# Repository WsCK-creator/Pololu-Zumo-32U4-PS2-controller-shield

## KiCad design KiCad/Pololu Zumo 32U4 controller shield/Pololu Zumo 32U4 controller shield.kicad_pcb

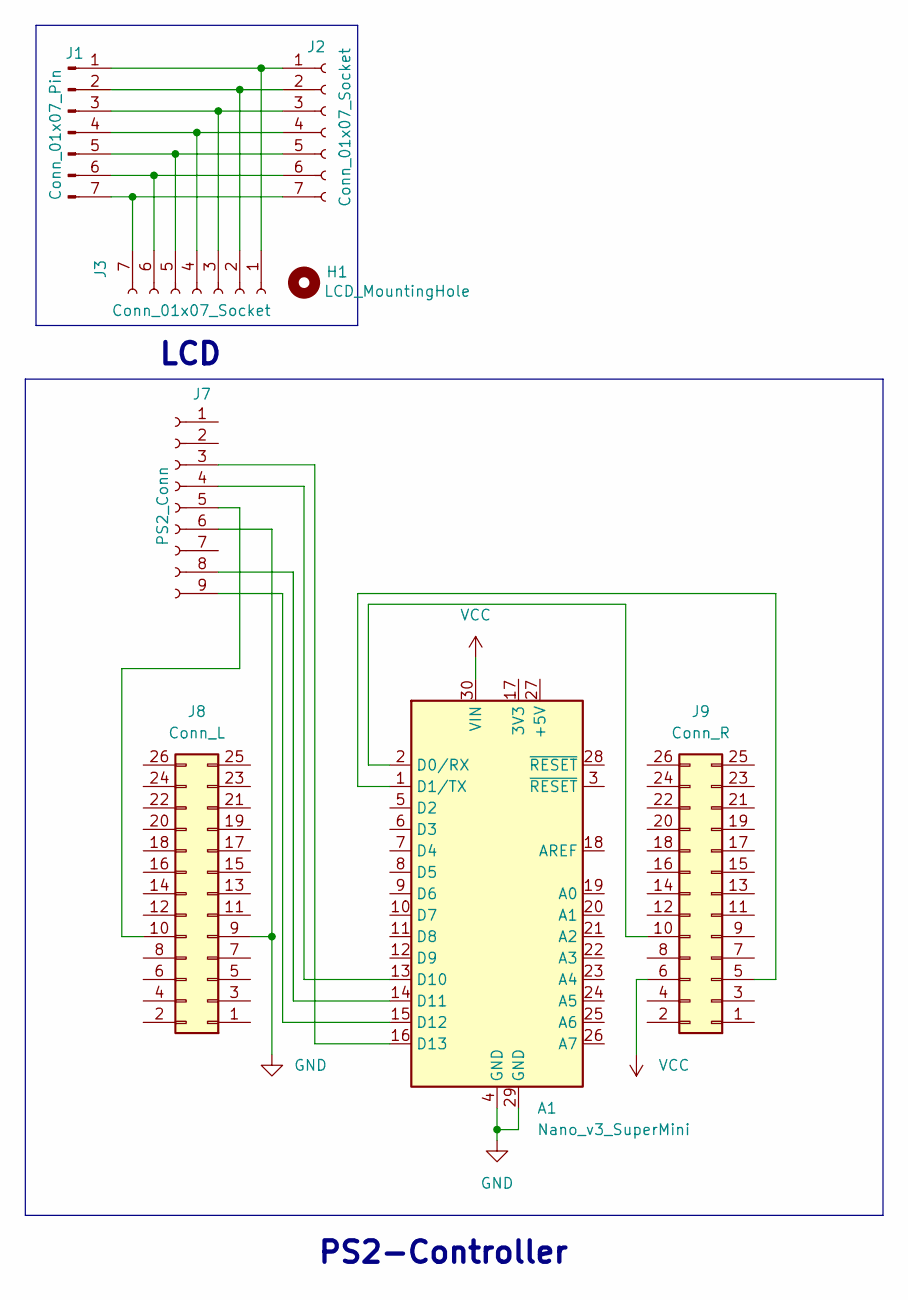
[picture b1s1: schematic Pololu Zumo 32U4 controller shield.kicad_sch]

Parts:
A1: Nano_v3_SuperMini; Nano_V3_SuperMini
H1: LCD_MountingHole; MountingHole_2.2mm_M2
J1: Conn_01x07_Pin; PinHeader_1x07_P2.54mm_Vertical
J2: Conn_01x07_Socket; PinSocket_1x07_P2.54mm_Vertical
J3: Conn_01x07_Socket; PinSocket_1x07_P2.54mm_Vertical_SMD_Pin1Left
J7: PS2_Conn; PS2_Controller_Conn
J8: Conn_L; PinHeader_2x13_P2.54mm_Vertical
J9: Conn_R; PinHeader_2x13_P2.54mm_Vertical

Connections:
GND: A1.4 (GND), A1.29 (GND), J7.6, J8.9
unnamed: A1.2 (D0/RX), J9.10
unnamed: A1.1 (D1/TX), J9.5
unnamed: A1.13 (D10), J7.4
unnamed: A1.14 (D11), J7.8
unnamed: A1.15 (D12), J7.9
unnamed: A1.16 (D13), J7.3
unnamed: J1.1, J2.1, J3.1
unnamed: J1.2, J2.2, J3.2
unnamed: J1.3, J2.3, J3.3
unnamed: J1.4, J2.4, J3.4
unnamed: J1.5, J2.5, J3.5
unnamed: J1.6, J2.6, J3.6
unnamed: J1.7, J2.7, J3.7
unnamed: J7.5, J8.10
VCC: A1.30 (VIN), J9.6

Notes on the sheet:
LCD
PS2-Controller

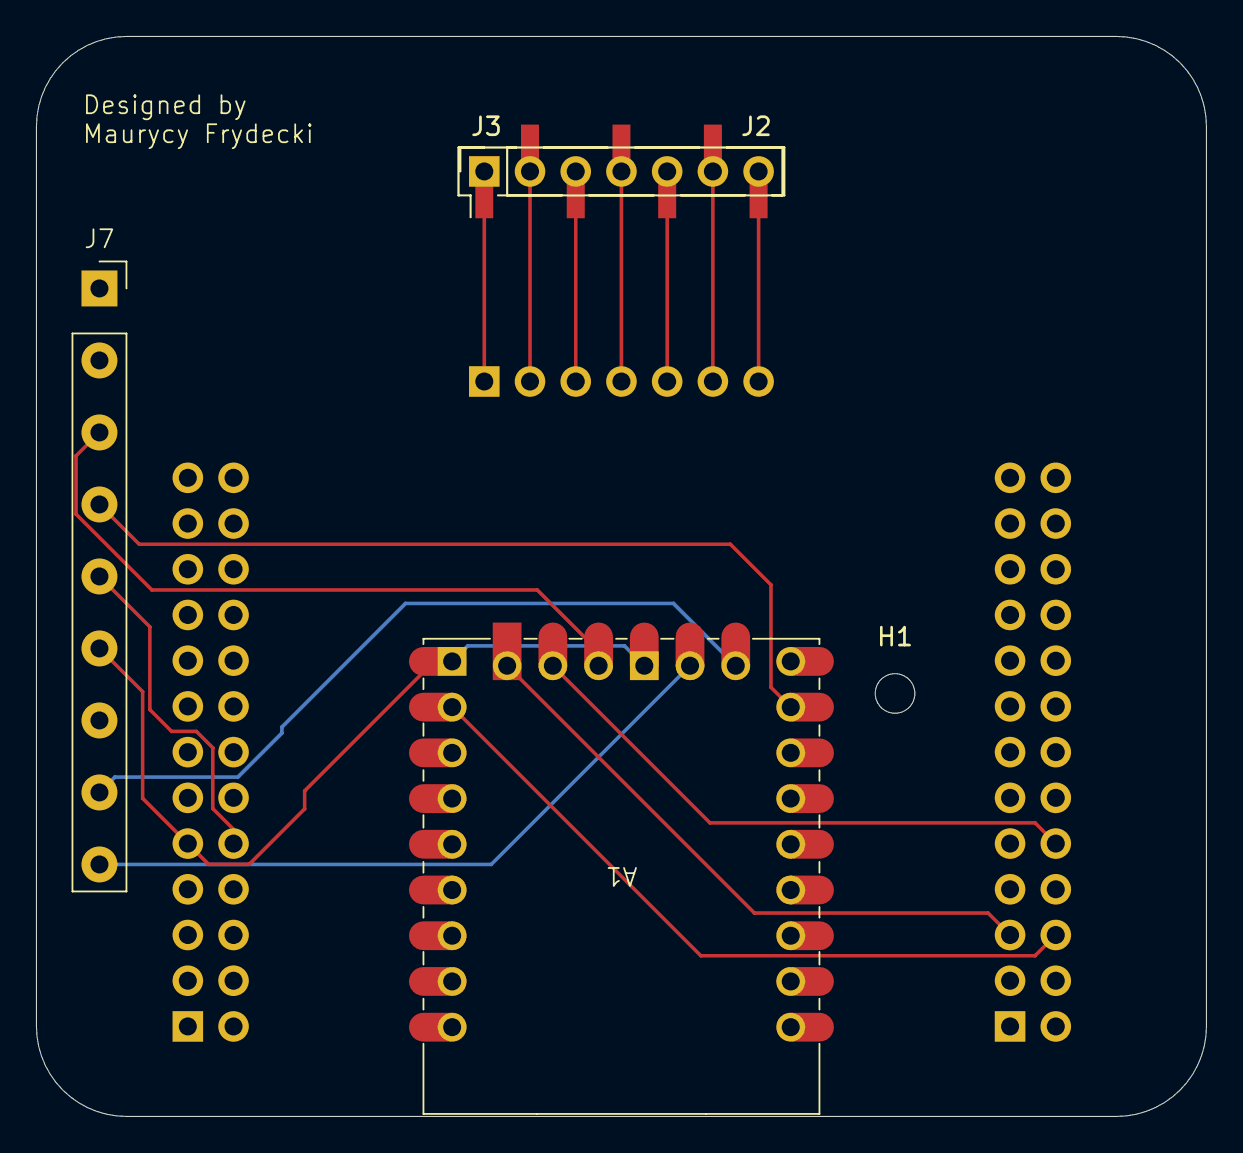
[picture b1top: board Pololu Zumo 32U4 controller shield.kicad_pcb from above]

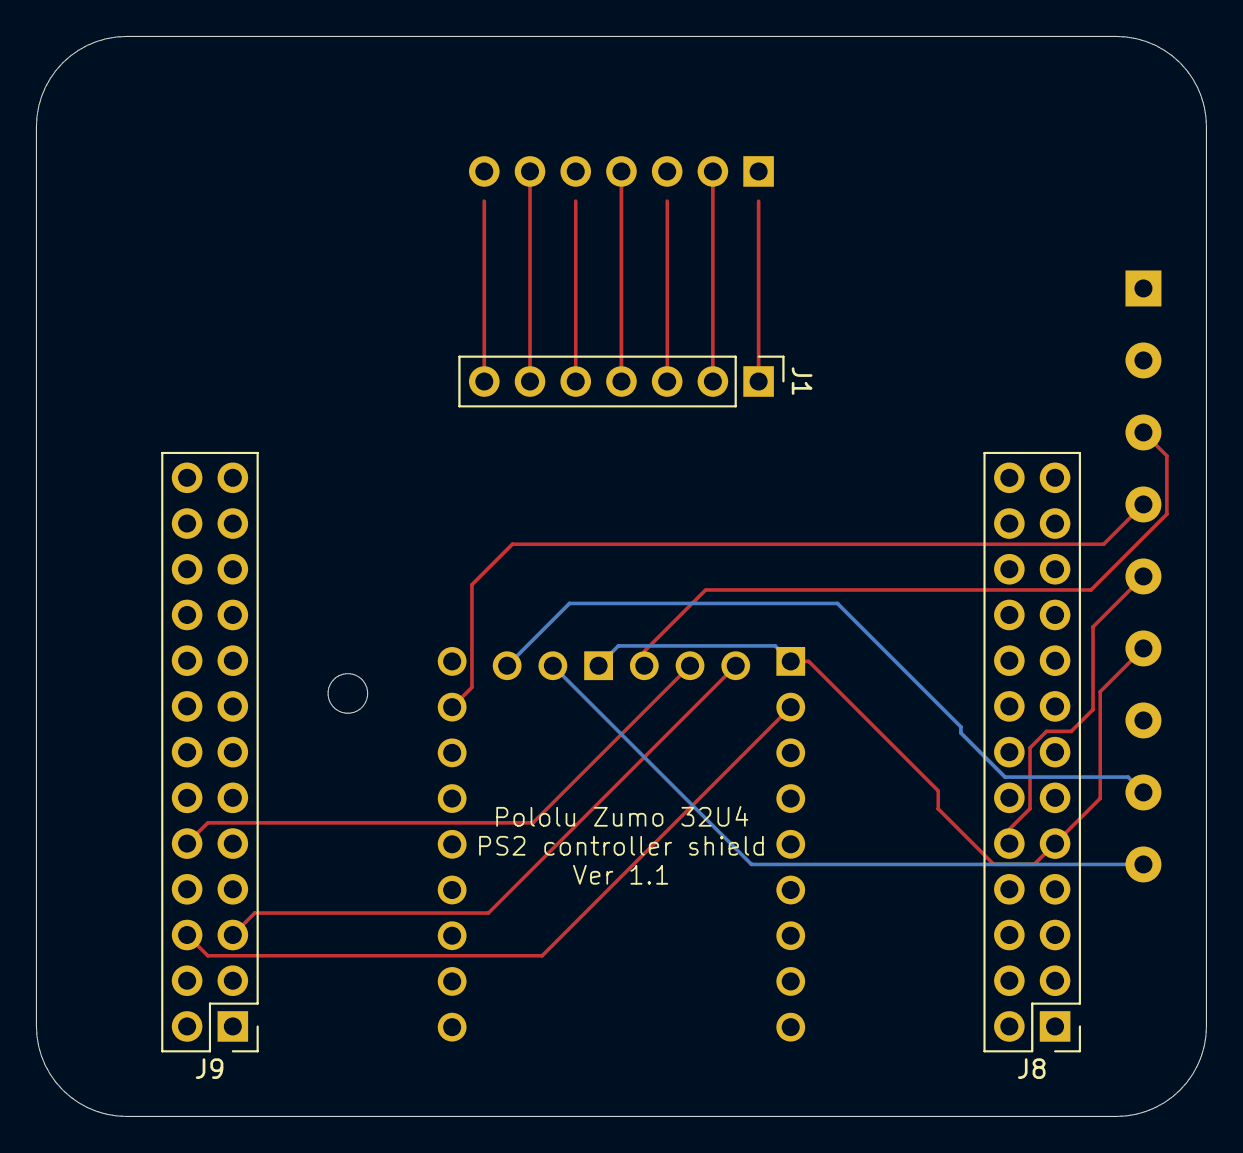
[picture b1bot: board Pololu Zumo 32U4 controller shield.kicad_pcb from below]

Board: 2 copper layers, 65.0 x 60.0 mm, 8 parts (3 on the bottom side), 16 nets.

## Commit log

2025-08-11 Added code and moved KiCad files
2025-10-19 Fixed display
2025-10-19 added gitignore
